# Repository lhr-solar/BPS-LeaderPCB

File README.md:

# BPS Leader Board

## Purpose 
This board runs the BPS system. It communicates with the [Voltage & Temperature Minion Boards](https://github.com/lhr-solar/BPS-MinionPCB) & [Amperes Board](https://github.com/lhr-solar/BPS-AmperesPCB) over ISOSPI, and the rest of the electrical system with CAN. It controls the [Contactors](https://dc-components.com/product/gigavac-gv241mab-400a-800vdc-dc-contactor/) & [Fans](https://github.com/lhr-solar/BPS-FanPCB) with 12V digital signals (PWM or just on/off). 

## Connectors
The board requires seven connectors:
* One 2-pin Power Connector (+12V, PWRGND)
* One 2-pin strobe light connector (+12V, PWRGND)
* One 4-pin contactor connector (+12V, PWRGND, aux1, aux2)
    * The aux pins detect if the Contactor is opened or closed through an Open Drain input.
* One 4-pin Amperes board connector (+12V, PWRGND, IP, IM)
* One 4-pin CAN connector (isolated +5V, isolated GND, CAN high, CAN low)
* One 2-pin Minion connector (IP, IM)
* One 2x4-pin fan connector (4x +12V, 4x PWRGND)

## Lights
* An LED next to the contactor pin turns on when the Contactors are closed
* An LED next to the Power Connector turns on when 12V is applied to the board
* The column of LED's in the middle of the board are used to provide debugging information

## BOM
https://www.mouser.com/ProjectManager/ProjectDetail.aspx?AccessID=ebf45c0b24

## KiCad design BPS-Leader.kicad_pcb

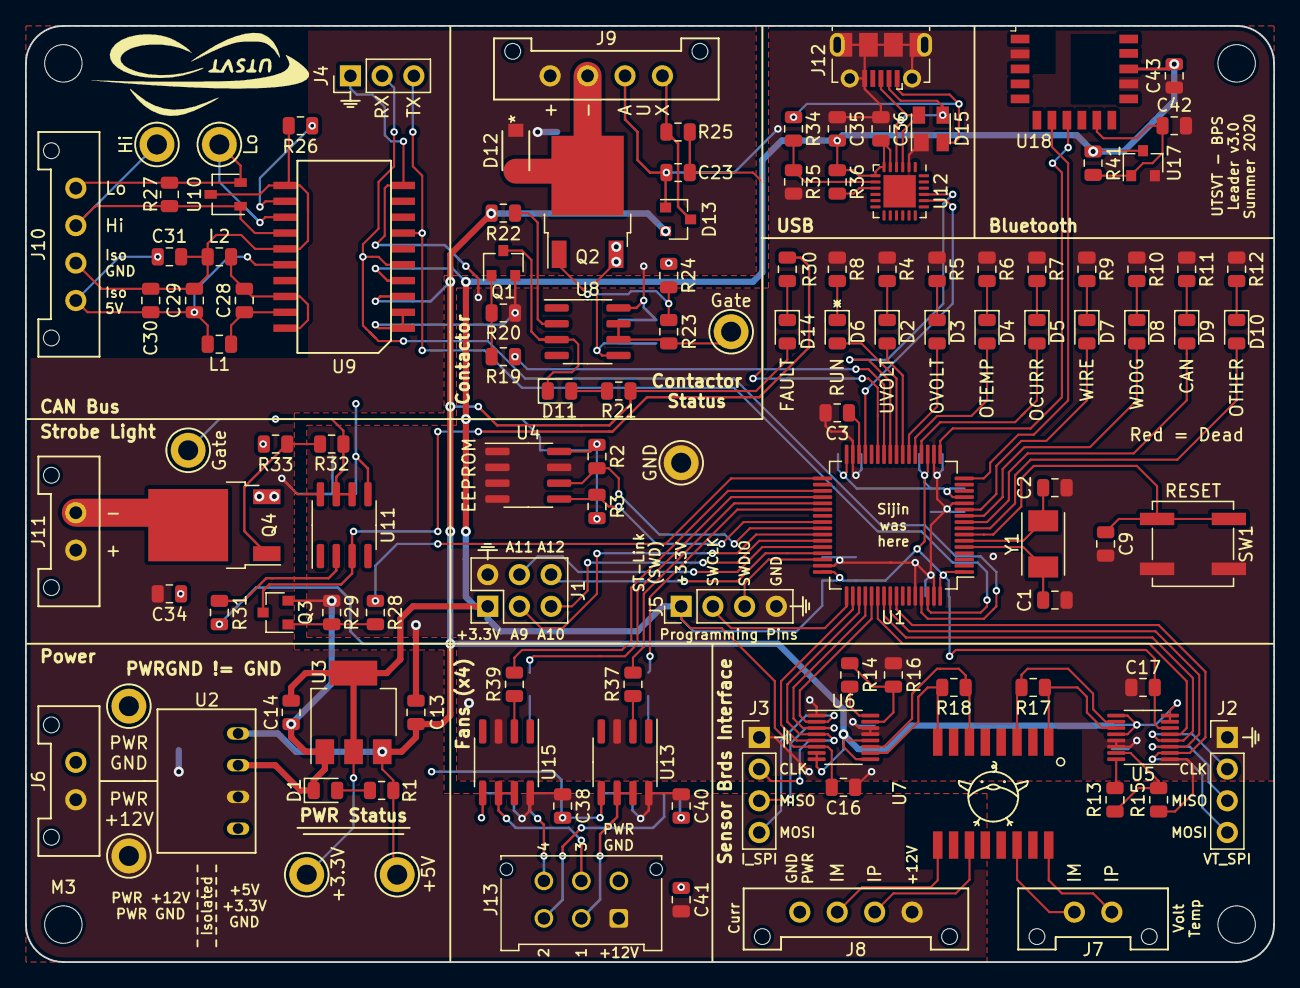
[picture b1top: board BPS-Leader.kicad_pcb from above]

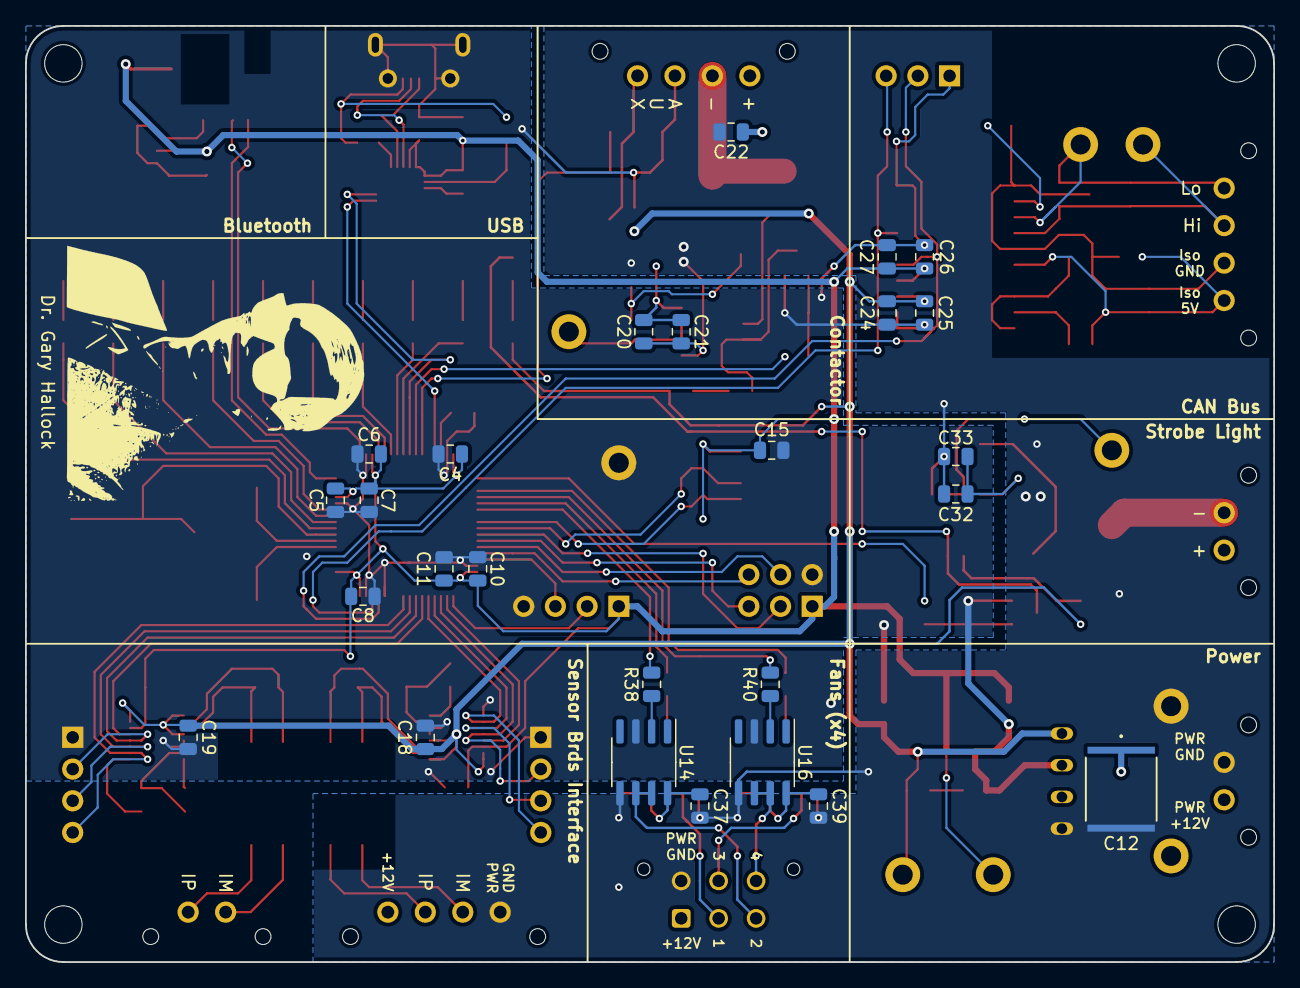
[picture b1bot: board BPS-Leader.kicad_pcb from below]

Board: 2 copper layers, 100.0 x 75.0 mm, 153 parts (27 on the bottom side), 105 nets.

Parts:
C1, C2: 12p; C_0805_2012Metric
C3, C11, C35: 4.7u; C_0805_2012Metric
C4, C5, C6, C8, C9, C10, C15, C16, C17, C18, C19, C20, C25, C26, C30, C32, C36, C37, C38, C39, C40, C43: 0.1u; C_0805_2012Metric
C7, C22, C23, C34, C42: 1u; C_0805_2012Metric
C12: 10u; C_2220_5750Metric
C13, C14, C21, C24, C29, C33, C41: 10u; C_0805_2012Metric
C27, C31: 0.01u; C_0805_2012Metric
C28: 0.22u; C_0805_2012Metric
D1: PowerOn; LED_0805_2012Metric
D2: UVolt; LED_0805_2012Metric
D3: OVolt; LED_0805_2012Metric
D4: OTemp; LED_0805_2012Metric
D5: OCurr; LED_0805_2012Metric
D6: Heartbeat; LED_0805_2012Metric
D7: Wire; LED_0805_2012Metric
D8: WDError; LED_0805_2012Metric
D9: CANError; LED_0805_2012Metric
D10: Other; LED_0805_2012Metric
D11: ContactorEn; LED_0805_2012Metric
D12: V2F22HM3/H; V2F22HM
D13: BAS70-04; SOT-23
D14: Fault; LED_0805_2012Metric
D15: SP0503BAHTG; SOT-143
J1: GPIO Analyzer; PinHeader_2x03_P2.54mm_Vertical
J2: Volt/Temp SPI Analyzer; PinHeader_1x04_P2.54mm_Vertical
J3: Current SPI Analyzer; PinHeader_1x04_P2.54mm_Vertical
J4: CAN Analyzer; PinHeader_1x03_P2.54mm_Vertical
J5: SWD; PinHeader_1x04_P2.54mm_Vertical
J6: PowerConn; Molex_MicroFit3.0_1x2xP3.00mm_PolarizingPeg_Vertical
J7: MinionConn; Molex_MicroFit3.0_1x2xP3.00mm_PolarizingPeg_Vertical
J8: CurrentConn; Molex_MicroFit3.0_1x4xP3.00mm_PolarizingPeg_Vertical
J9: ContactorConn; Molex_MicroFit3.0_1x4xP3.00mm_PolarizingPeg_Vertical
J10: CAN_Out; Molex_MicroFit3.0_1x4xP3.00mm_PolarizingPeg_Vertical
J11: ErrorLightConn; Molex_MicroFit3.0_1x2xP3.00mm_PolarizingPeg_Vertical
J12: USB_B_Micro; USB_Micro-B_Molex-105017-0001
J13: FanBrdConn; Molex_Micro-Fit_3.0_43045-0612_2x03_P3.00mm_Vertical
L1, L2: 2k; L_0805_2012Metric
LOGO1: Dr. Hallock; Hallock_Image_Small
LOGO2: UTSVT Logo; UTSVT_Logo_Symbol
MH1, MH2, MH3, MH4: M.3; MountingHole_3mm
Q1, Q3: NTR4003NT1G; SOT-23
Q2, Q4: VND5N07-E; TO-252-2
R1, R21: 1.5k; R_0805_2012Metric
R2, R3, R41: 4.7k; R_0805_2012Metric
R4, R5, R6, R7, R9, R10, R11, R12: 750; R_0805_2012Metric
R8: 680; R_0805_2012Metric
R13, R14: 806; R_0805_2012Metric
R15, R16: 1.21k; R_0805_2012Metric
R17, R18, R27: 120; R_0805_2012Metric
R19, R23, R26, R28, R32: 0; R_0805_2012Metric
R20, R24, R29, R33: 10k; R_0805_2012Metric
R22, R31: 470; R_0805_2012Metric
R25, R36: 1k; R_0805_2012Metric
R30: 1.6k; R_0805_2012Metric
R34: 22.1k; R_0805_2012Metric
R35: 47.5k; R_0805_2012Metric
R37, R38, R39, R40: 118; R_0805_2012Metric
SW1: B3SL-1002P; SW_SPST_B3SL-1002P
TP1: +12V_TP; TestPoint_Keystone_5005-5009_Compact
TP2: GNDPWR_TP; TestPoint_Keystone_5005-5009_Compact
TP3: +5V_TP; TestPoint_Keystone_5005-5009_Compact
TP4: GND_TP; TestPoint_Keystone_5005-5009_Compact
TP5: +3.3V_TP; TestPoint_Keystone_5005-5009_Compact
TP6: ContactorGate_TP; TestPoint_Keystone_5005-5009_Compact
TP7: CAN_H; TestPoint_Keystone_5005-5009_Compact
TP8: CAN_L; TestPoint_Keystone_5005-5009_Compact
TP9: StrobeLightGate_TP; TestPoint_Keystone_5005-5009_Compact
U1: STM32F413RHTx; LQFP-64_10x10mm_P0.5mm
U2: RI3-1205S; RI3_DC_Converter
U3: NCP1117-3.3_SOT223; SOT-223-3_TabPin2
U4: M24128; SOIC-8_3.9x4.9mm_P1.27mm
U5, U6: LTC6820; MSOP-16_3x4mm_P0.5mm
U7: HX1188FNL; HXXXX
U8, U11, U13, U14, U15, U16: SI8261ABC-IS; SOIC-8_3.9x4.9mm_P1.27mm
U9: ADM3055E; SOIC-20W_7.5x15.4mm_Pitch1.27mm
U10: CDSOT23-T24CAN; SOT-23W
U12: CP2102N-A01-GQFN24; QFN-24-1EP_4x4mm_P0.5mm_EP2.6x2.6mm
U17: MCP112; SOT-23
U18: RN4871-I; Microchip_RN4871
Y1: 8M; Crystal_SMD_TXC_7A-2Pin_5x3.2mm

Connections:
+3V3: C4.1, C5.1, C6.1, C7.1, C8.1, C10.1, C11.1, C14.1, C15.1, C16.1, C17.1, C26.1, C27.1, C35.1, C36.1, C43.2, J1.1, J5.1, R2.1, R3.1, R36.1, R41.1, TP5.1, U1.1, U1.13, U1.19, U1.32, U1.48, U1.64, U3.2, U4.8, U5.6, U6.6, U9.4, U12.5, U12.6, U12.7, U17.3, U18.14
+5V: C13.1, C18.1, C19.1, C24.1, C25.1, D13.2, D14.2, R1.1, R21.1, R22.2, R31.2, TP3.1, U2.4, U3.3, U5.7, U5.8, U5.9, U5.12, U6.7, U6.8, U6.9, U6.12, U9.3
+12V: C12.1, C20.1, C21.1, C22.2, C32.1, C33.1, C34.2, C37.1, C38.1, C39.1, C40.1, C41.1, D12.1, J6.1, J8.1, J9.1, J11.1, J13.1, TP1.1, U2.2, U8.8, U11.8, U13.8, U14.8, U15.8, U16.8
/CAN1_RX: J4.2, U1.61, U9.5
/CAN1_TX: J4.3, U1.62, U9.7
/CAN/CAN_H: J10.3, R27.2, TP7.1, U9.14, U10.1
/CAN/CAN_L: J10.4, R27.1, TP8.1, U9.13, U10.2
/CAN/RSlope: R26.1, U9.12
/Contactor Driver/CONTACTOR_V-: D12.2, J9.2, Q2.2
/FAULT: R28.2, U1.33
/Fan Board Interface/FAN1: J13.2, U13.6, U13.7
/Fan Board Interface/FAN2: J13.3, U14.6, U14.7
/Fan Board Interface/FAN3: J13.5, U15.6, U15.7
/Fan Board Interface/FAN4: J13.6, U16.6, U16.7
/I2C3_SCL: R2.2, U1.41, U4.6
/I2C3_SDA: R3.2, U1.40, U4.5
/NRST: C9.1, SW1.1, U1.7
/OSC_IN: C1.1, U1.5, Y1.1
/OSC_OUT: C2.1, U1.6, Y1.2
/PA4: D5.2, U1.20
/PA5: D4.2, U1.21
/PA6: D3.2, U1.22
/PA7: D2.2, U1.23
/PA9: J1.3, U1.42
/PA10: J1.5, U1.43
/PA11: J1.4, U1.44
/PA12: J1.6, U1.45
/PA15: U1.50, U6.5
/PB0: R19.2, U1.26
/PB1: C23.1, R25.1, U1.27
/PC0: D10.2, U1.8
/PC1: D9.2, U1.9
/PC2: D8.2, U1.10
/PC3: D7.2, U1.11
/PC4: D6.2, U1.24
/PD2: U1.54, U5.5
/SPI1_CLK: J2.2, U1.55, U5.4
/SPI1_MISO: J2.3, U1.56, U5.3
/SPI1_MOSI: J2.4, U1.57, U5.2
/SPI3_CLK: J3.2, U1.51, U6.4
/SPI3_MISO: J3.3, U1.52, U6.3
/SPI3_MOSI: J3.4, U1.53, U6.2
/SWCLK: J5.2, U1.49
/SWDIO: J5.3, U1.46
/Sensor Boards Interface/I_IM: R18.2, U6.10, U7.8
/Sensor Boards Interface/I_IP: R18.1, U6.11, U7.6
/Sensor Boards Interface/VT_IM: R17.2, U5.10, U7.3
/Sensor Boards Interface/VT_IP: R17.1, U5.11, U7.1
/TIM3_CH1: R37.2, U1.37
/TIM3_CH2: R38.2, U1.38
/TIM12_CH1: R39.2, U1.35
/TIM12_CH2: R40.2, U1.36
/UART2_RX: U1.17, U18.8
/UART2_TX: U1.16, U18.7
/USART3_RX: U1.25, U12.21
/USART3_TX: U1.29, U12.20
GND: C1.2, C2.2, C3.2, C4.2, C5.2, C6.2, C7.2, C8.2, C9.2, C10.2, C11.2, C13.2, C14.2, C15.2, C16.2, C17.2, C18.2, C19.2, C23.2, C24.2, C25.2, C26.2, C27.2, C35.2, C36.2, C42.2, C43.1, D1.1, D13.1, D15.1, J1.2, J2.1, J3.1, J4.1, J5.4, J9.3, J12.5, J12.6, Q1.2, Q3.2, R4.2, R5.2, R6.2, R7.2, R8.2, R9.2, R10.2, R11.2, R12.2, R15.1, R16.1, R20.2, R29.2, R35.2, SW1.2, TP4.1, U1.12, U1.18, U1.31, U1.47, U1.60, U1.63, U2.3, U3.1, U4.1, U4.2, U4.3, U4.4, U4.7, U5.1, U5.13, U5.14, U6.1, U6.13, U6.14, U9.1, U9.2, U9.10, U12.2, U12.25, U13.3, U14.3, U15.3, U16.3, U17.2, U18.2, U18.13
GNDPWR: C12.2, C20.2, C21.2, C22.1, C32.2, C33.2, C34.1, C37.2, C38.2, C39.2, C40.2, C41.2, J6.2, J8.4, J13.4, Q2.3, Q4.3, R24.2, R33.2, TP2.1, U2.1, U8.5, U11.5, U13.5, U14.5, U15.5, U16.5
unnamed: C3.1, U1.30
unnamed: C28.1, L1.2, U9.19
unnamed: C28.2, L2.2, U9.18, U9.20
unnamed: C29.1, C30.1, C31.1, J10.1, L1.1, U9.16
unnamed: C29.2, C30.2, C31.2, J10.2, L2.1, R26.2, U9.11, U9.15, U10.3
unnamed: C42.1, R41.2, U17.1, U18.10
unnamed: D1.2, R1.2
unnamed: D2.1, R4.1
unnamed: D3.1, R5.1
unnamed: D4.1, R6.1
unnamed: D5.1, R7.1
unnamed: D6.1, R8.1
unnamed: D7.1, R9.1
unnamed: D8.1, R10.1
unnamed: D9.1, R11.1
unnamed: D10.1, R12.1
unnamed: D11.1, Q1.3, U8.3
unnamed: D11.2, R21.2
unnamed: D13.3, J9.4, R25.2
unnamed: D14.1, R30.1
unnamed: D15.2, J12.1, R34.2
unnamed: D15.3, J12.2, U12.4
unnamed: D15.4, J12.3, U12.3
unnamed: J7.1, U7.16
unnamed: J7.2, U7.14
unnamed: J8.2, U7.11
unnamed: J8.3, U7.9
unnamed: J11.2, Q4.2
unnamed: Q1.1, R19.1, R20.1
unnamed: Q2.1, R23.1, R24.1
unnamed: Q3.1, R28.1, R29.1
unnamed: Q3.3, R30.2, U11.3
unnamed: Q4.1, R32.1, R33.1
unnamed: R13.1, R15.2, U5.15
unnamed: R13.2, U5.16
unnamed: R14.1, R16.2, U6.15
unnamed: R14.2, U6.16
unnamed: R22.1, U8.2
unnamed: R23.2, TP6.1, U8.6, U8.7
unnamed: R31.1, U11.2
unnamed: R32.2, TP9.1, U11.6, U11.7
unnamed: R34.1, R35.1, U12.8
unnamed: R36.2, U12.9
unnamed: R37.1, U13.2
unnamed: R38.1, U14.2
unnamed: R39.1, U15.2
unnamed: R40.1, U16.2

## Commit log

2020-08-02 Set up for own repository
2020-08-02 Updates gitignore
2020-08-06 Changes version number to v3.0
2020-08-06 Moves BAS70-04 to utsvt-chips because other systems use this component
2020-08-07 Adds mouser cart link
2020-08-07 Adds correct mouser link. previous one had minion link
2020-08-12 Makes LED silkscreen labels consistent. Changed Other to all caps OTHER
2020-08-12 Updates viewable files (PDF, PNG) so one can view in github without cloning
2020-08-12 Renames project to match repo name
2020-08-13 Updates BAS70-04 footprint for Contactor auxillary interface
2020-08-13 Updates common library submodule
2020-08-17 Changes clearance from 0.127 to .2mm:
2020-09-01 Renames project to not include PCB
2020-09-19 Adds HX1188 component to common library
2020-09-19 Deletes unused Misc File
2020-09-19 Renames Reset button
2020-10-03 Adds QuAC
2021-03-07 Adds 3d model components
2023-04-21 Updated to KiCAD 6
2023-04-29 Update repo to only use one common library
2023-05-05 Fixed all symbol issues
2023-05-06 Added ReadME Documentation
2023-05-06 Added version control notes to main schematic
2023-05-28 Following right branch on submodule

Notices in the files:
parts and their libraries:
Copyright 2016 Accelerated Designs. All rights reserved.
